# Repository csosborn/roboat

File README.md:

# Roboat!

An autonomous, solar-powered boat. An RP2040 microcontroller handles power monitoring and control and supervises a Raspberry Pi, which provides data storage, navigation, planning, and communications.

## Design documents

- [Compute.md](Compute.md): compute architecture and the power-management state machine
- [PowerSystem.md](PowerSystem.md): battery, charge controller, and solar array selection
- [SolarArrayTrade.md](SolarArrayTrade.md): solar array trade study

## Repository layout

| Path | Contents |
| --- | --- |
| `src/micro/` | MicroPython code for the RP2040 Feather (power FSM, Victron MPPT, INA260, Pi link) |
| `src/pi/` | Raspberry Pi monitor service, TIG stack (Telegraf/InfluxDB/Grafana), and systemd units; see [setup notes](src/pi/TIG/setup.md) |
| `src/build-tools/` | Docker container for building custom MicroPython firmware |
| `printed_parts/` | STL files for 3D-printed parts |
| `take1/` | The original Arduino/Eagle-based attempt, kept for reference |

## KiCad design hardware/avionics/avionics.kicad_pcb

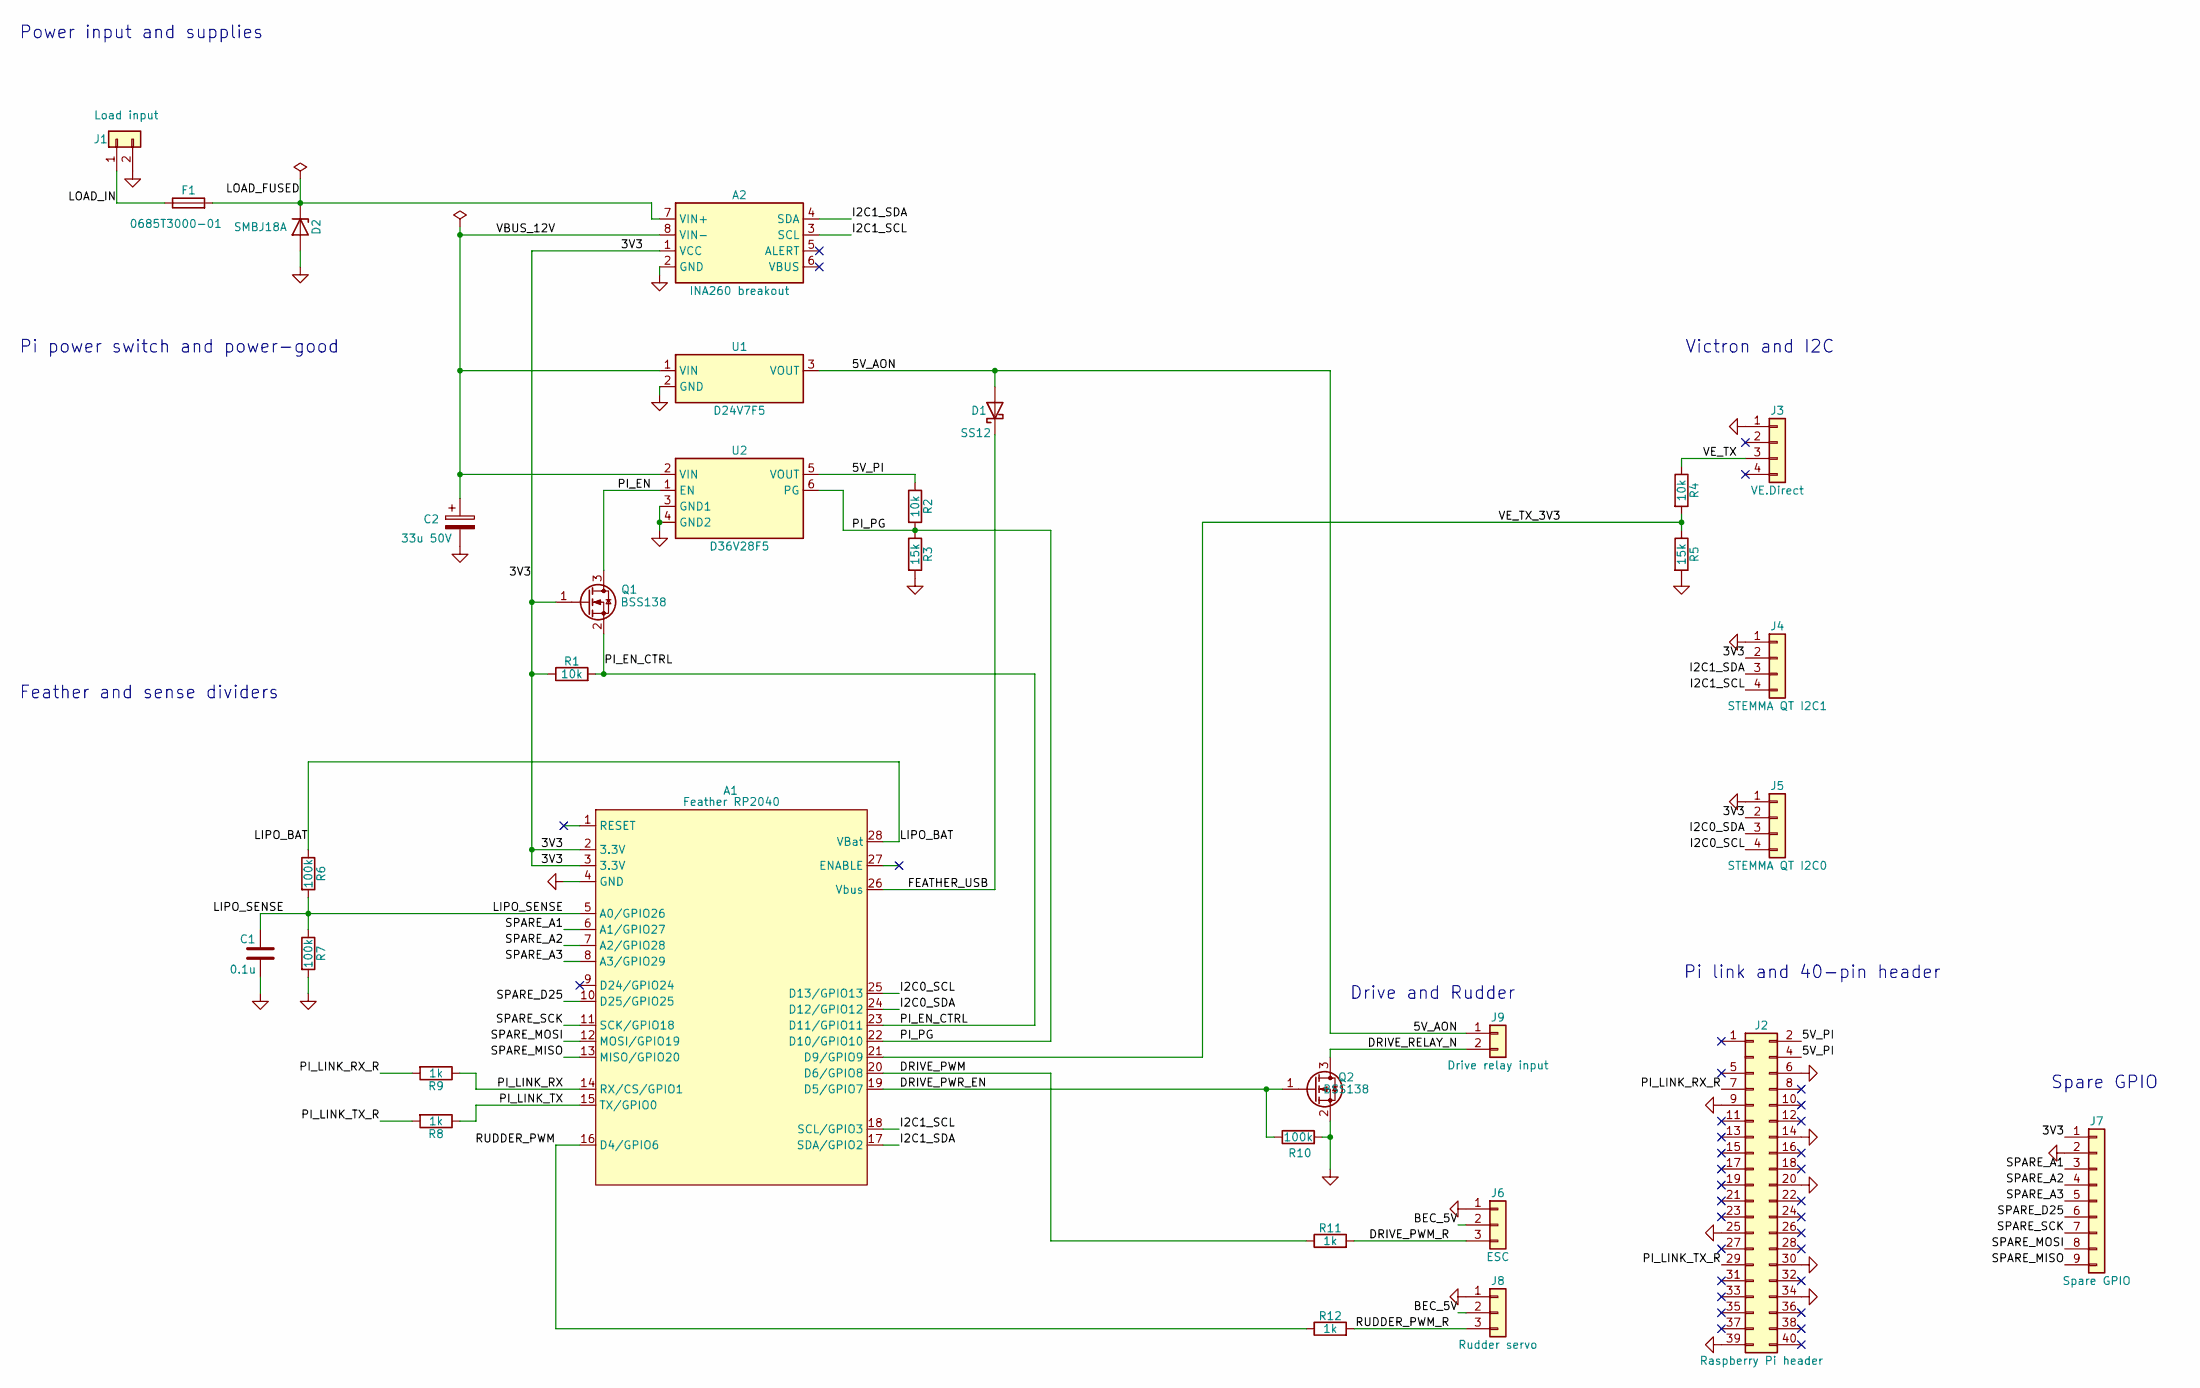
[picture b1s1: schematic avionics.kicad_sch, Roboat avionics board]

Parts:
A1: Feather RP2040; Adafruit-Feather-RP2040
A2: INA260 breakout; Adafruit_INA260_Breakout
C1: 0.1u; C_0805_2012Metric
C2: 33u 50V; CP_Radial_D6.3mm_P2.50mm
D1: SS12; D_SMA
D2: SMBJ18A; D_SMB
F1: 0685T3000-01; Fuse_1206_3216Metric_Pad1.42x1.75mm_HandSolder
J1: Load input; AMASS_XT30PW-F_1x02_P2.50mm_Horizontal
J2: Raspberry Pi header; PinSocket_2x20_P2.54mm_Vertical_NoPin3
J3: VE.Direct; JST_PH_B4B-PH-K_1x04_P2.00mm_Vertical
J4: STEMMA QT I2C1; JST_SH_BM04B-SRSS-TB_1x04-1MP_P1.00mm_Vertical
J5: STEMMA QT I2C0; JST_SH_BM04B-SRSS-TB_1x04-1MP_P1.00mm_Vertical
J6: ESC; PinHeader_1x03_P2.54mm_Vertical
J7: Spare GPIO; PinHeader_1x09_P2.54mm_Vertical
J8: Rudder servo; PinHeader_1x03_P2.54mm_Vertical
J9: Drive relay input; JST_PH_B2B-PH-K_1x02_P2.00mm_Vertical
Q1, Q2: BSS138; SOT-23
R1, R2, R4: 10k; R_0805_2012Metric
R3, R5: 15k; R_0805_2012Metric
R6, R7, R10: 100k; R_0805_2012Metric
R8, R9, R11, R12: 1k; R_0805_2012Metric
U1: D24V7F5; Pololu_D24V7F5
U2: D36V28F5; Pololu_D36V28F5

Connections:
/3V3: A1.2 (3.3V), A1.3 (3.3V), A2.1 (VCC), J4.2, J5.2, J7.1, Q1.1 (G), R1.1
/5V_AON: D1.2 (A), J9.1, U1.3 (VOUT)
/5V_PI: J2.2, J2.4, R2.1, U2.5 (VOUT)
/BEC_5V: J6.2, J8.2
/DRIVE_PWM: A1.20 (D6/GPIO8), R11.1
/DRIVE_PWM_R: J6.3, R11.2
/DRIVE_PWR_EN: A1.19 (D5/GPIO7), Q2.1 (G), R10.1
/DRIVE_RELAY_N: J9.2, Q2.3 (D)
/FEATHER_USB: A1.26 (Vbus), D1.1 (K)
/I2C0_SCL: A1.25 (D13/GPIO13), J5.4
/I2C0_SDA: A1.24 (D12/GPIO12), J5.3
/I2C1_SCL: A1.18 (SCL/GPIO3), A2.3 (SCL), J4.4
/I2C1_SDA: A1.17 (SDA/GPIO2), A2.4 (SDA), J4.3
/LIPO_BAT: A1.28 (VBat), R6.1
/LIPO_SENSE: A1.5 (A0/GPIO26), C1.1, R6.2, R7.1
/LOAD_FUSED: A2.7 (VIN+), D2.1 (K), F1.2
/LOAD_IN: F1.1, J1.1
/PI_EN: Q1.3 (D), U2.1 (EN)
/PI_EN_CTRL: A1.23 (D11/GPIO11), Q1.2 (S), R1.2
/PI_LINK_RX: A1.14 (RX/CS/GPIO1), R9.1
/PI_LINK_RX_R: J2.7, R9.2
/PI_LINK_TX: A1.15 (TX/GPIO0), R8.1
/PI_LINK_TX_R: J2.29, R8.2
/PI_PG: A1.22 (D10/GPIO10), R2.2, R3.1, U2.6 (PG)
/RUDDER_PWM: A1.16 (D4/GPIO6), R12.1
/RUDDER_PWM_R: J8.3, R12.2
/SPARE_A1: A1.6 (A1/GPIO27), J7.3
/SPARE_A2: A1.7 (A2/GPIO28), J7.4
/SPARE_A3: A1.8 (A3/GPIO29), J7.5
/SPARE_D25: A1.10 (D25/GPIO25), J7.6
/SPARE_MISO: A1.13 (MISO/GPIO20), J7.9
/SPARE_MOSI: A1.12 (MOSI/GPIO19), J7.8
/SPARE_SCK: A1.11 (SCK/GPIO18), J7.7
/VBUS_12V: A2.8 (VIN-), C2.1, U1.1 (VIN), U2.2 (VIN)
/VE_TX: J3.3, R4.1
/VE_TX_3V3: A1.21 (D9/GPIO9), R4.2, R5.1
GND: A1.4 (GND), A2.2 (GND), C1.2, C2.2, D2.2 (A), J1.2, J2.6, J2.9, J2.14, J2.20, J2.25, J2.30, J2.34, J2.39, J3.1, J4.1, J5.1, J6.1, J7.2, J8.1, Q2.2 (S), R3.2, R5.2, R7.2, R10.2, U1.2 (GND), U2.3 (GND1), U2.4 (GND2)

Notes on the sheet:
Victron and I2C
Power input and supplies
Drive and Rudder
Pi power switch and power-good
Feather and sense dividers
Spare GPIO
Pi link and 40-pin header

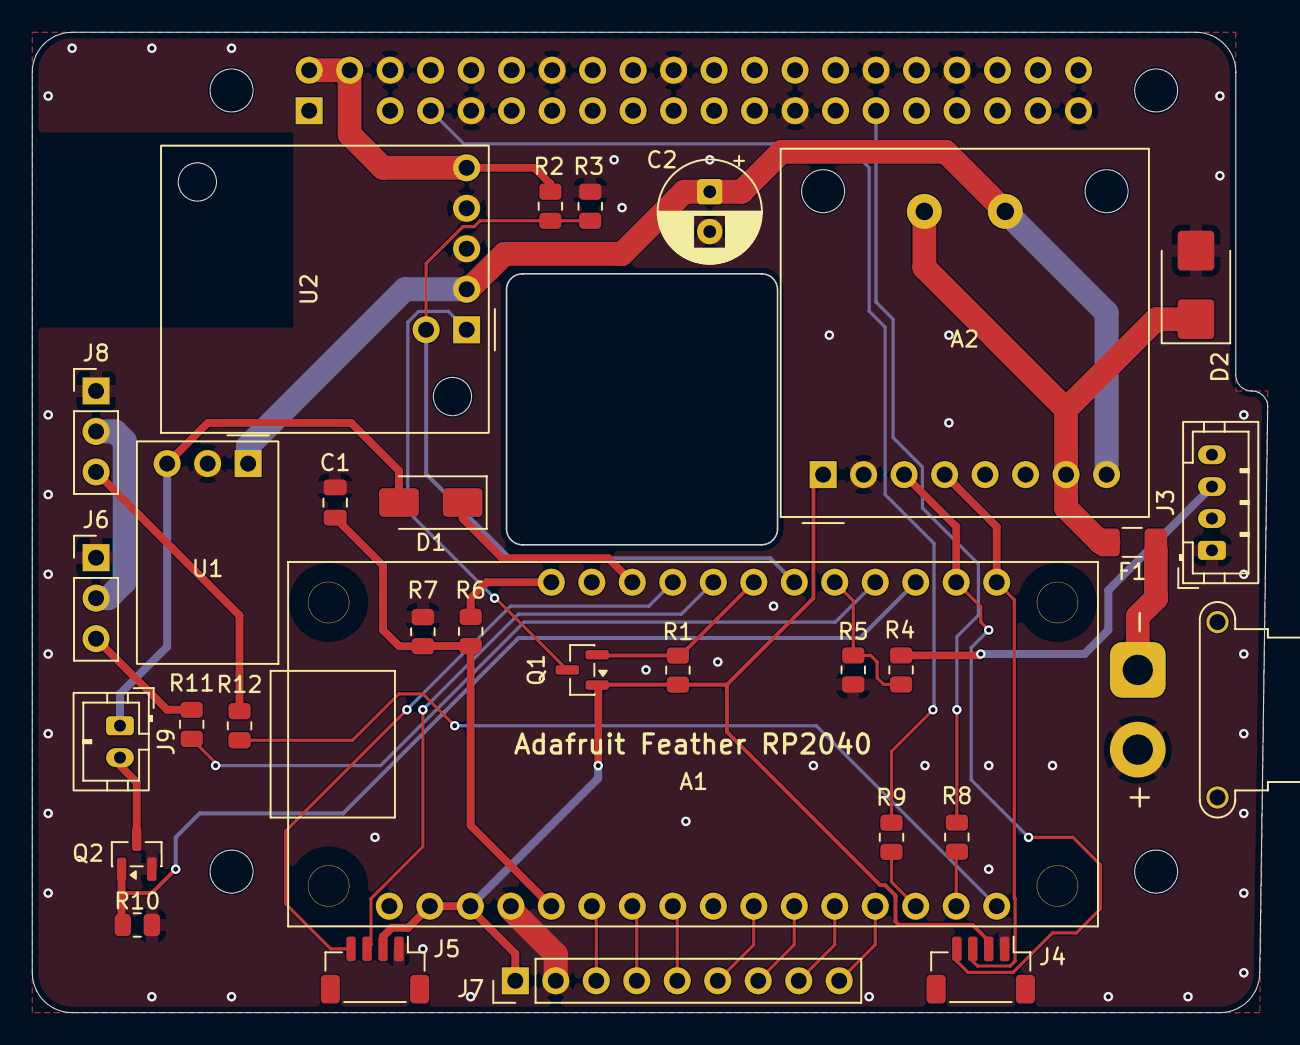
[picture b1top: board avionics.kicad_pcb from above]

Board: 2 copper layers, 77.5 x 61.5 mm, 36 parts (1 on the bottom side), 37 nets.

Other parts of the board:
H1, H2, H3, H4: MountingHole_2.7mm_M2.5

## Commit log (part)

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2017-09-11 First commit, with notes and initial Arduino code skeleton.
2017-10-14 Tinkering with the Pilot module firmware.
2017-11-06 Added PCB and related Eagle libraries.
2017-11-06 Updated Arduino code with new pin assignments from PCB.
2017-11-13 All parts accounted for.
2017-12-23 Added initial AHRS state machine to Pilot module.
2017-12-24 Factored Roboat::StateMachine out of Roboat::AHRS.
2017-12-24 Added PowerManager state machine to Pilot module.
2017-12-26 Rearranged initializer lists to avoid reorder warnings
2018-01-02 Refactoring, cleanup, const-correctness
2018-01-08 Factored GPS code into RoboatGPSManager state machine
2018-01-08 Sketched out Captain state machine. More refactoring.
2018-01-27 Small corrections.
2019-03-03 Initial captain skeleton and connection to helm.
2019-03-04 Cleaned up CMake/Conan approach, added SQLite.
2019-03-04 Early experiments with SQLite-based persistence.
2019-03-05 Added prepared statement step() method.
2024-10-24 Move abandoned prehistory to take1 directory.
2024-10-24 Some basic notes on Roboat, take 2.
2024-10-24 Basic containerized TIG stack.
2024-10-24 Don't ignore src/pi.
2024-10-24 Initial scratch work on RP2040.
2024-10-24 Initial scratch work on Pi side.
2024-10-24 Omit Grafana pending memory upgrade.
2024-12-02 TIG stack and supporting systemd units.
2024-12-02 RP2040 micropython lib directory.
2024-12-02 RPi-based monitor program (not yet containerized)
2024-12-02 Some updated notes on the power control state machine.
2024-12-02 Grafana dashboard definition.
2024-12-02 A bunch of disorganized changes to the RP2040 code.
2024-12-14 Added micropython-builder container.
2024-12-14 Remove incorrectly added submodules.
2025-06-19 A initial quite mediocre SoC estimator.
2025-06-19 Avionics testbed and sync util.

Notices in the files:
parts and their libraries:
Adafruit INA260 breakout (product 4226), socketed on a 1x8 0.1 in header. Optional 5.08 mm pads repeat VIN+/VIN- at the terminal block. M2.5 holes for standoffs. Geometry from adafruit/Adafruit-INA260-PCB (CC BY-SA 3.0).
